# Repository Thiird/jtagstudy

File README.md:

# jtagstudy
In my journey of embedded systems, I felt like I was lacking embedded software development experience, and so to gain some, I decided to implement some of the [JTAG IEE 1149.1](https://en.wikipedia.org/wiki/JTAG) functionalities as [bit-bang](https://en.wikipedia.org/wiki/Bit_banging) routines.

I choose JTAG as the protocol to bit-bang because it's relatively simple to understand, useful for a lot of things used across different architectures and it's an industry standard.

I used AVR MCU's because that's what I had at my disposal, no need to spend extra money on a fancy STM32.

# Overview

Here is a picture of my inital setup:

I used an [ATmega 32u4](http://ww1.microchip.com/downloads/en/DeviceDoc/Atmel-7766-8-bit-AVR-ATmega16U4-32U4_Datasheet.pdf) from an [Arduino Micro](https://store.arduino.cc/products/arduino-micro) board as the the main MCU to which I uploaded code via the [USBasp](https://www.fischl.de/usbasp/) ISP programmer and [avrdude](https://www.nongnu.org/avrdude/). I also implemented the USART interface (TX only) to be able to print to the serial monitor the result of the code.
To test the code, I initially connected the four GPIO bit-banging pins to the JTAG interface of the 32u4 itself, once that was working, I used a custom PCB designed in [KiCad](https://www.kicad.org/) to extend the JTAG chain with two more TAPs and test the code again. The custom PCB is a breakout for another ATmega 32u4 and an [AT90USB1286](http://ww1.microchip.com/downloads/en/DeviceDoc/doc7593.pdf) Extending the JTAG chain revealed some bugs which I managed to solve in a couple of days.

The PCB had some mistakes which were solved by bridging some connections and whatnot.

Here is a picture of my final setup:

I learned a lot of things while doing this project, not only software related, but also hardware, because this was my first time using an [oscilloscope](https://eleshop.eu/owon-sds1104.html), which I used to debug the signals I was bit-banging.

# Functionalities

- **JTAG TAP chain length**

    Uses the **BYPASS** instruction to check how many Test Acces Points (TAP's) are connected to the JTAG interface.

- **IDCODE scan**

    Prints to serial in detail the **IDCODE** of all the TAPs found in the JTAG Chain.

- **JTAG discovery**

    Given a set of GPIO pins, the four JTAG signal (TDI,TDO,TMS,TCK) are applied in different combinations to find if there is a JTAG interface on four of those pins.

# Credits
This was project was inspired by the [JTAGulator](https://github.com/grandideastudio/jtagulator) by Joe Grand.

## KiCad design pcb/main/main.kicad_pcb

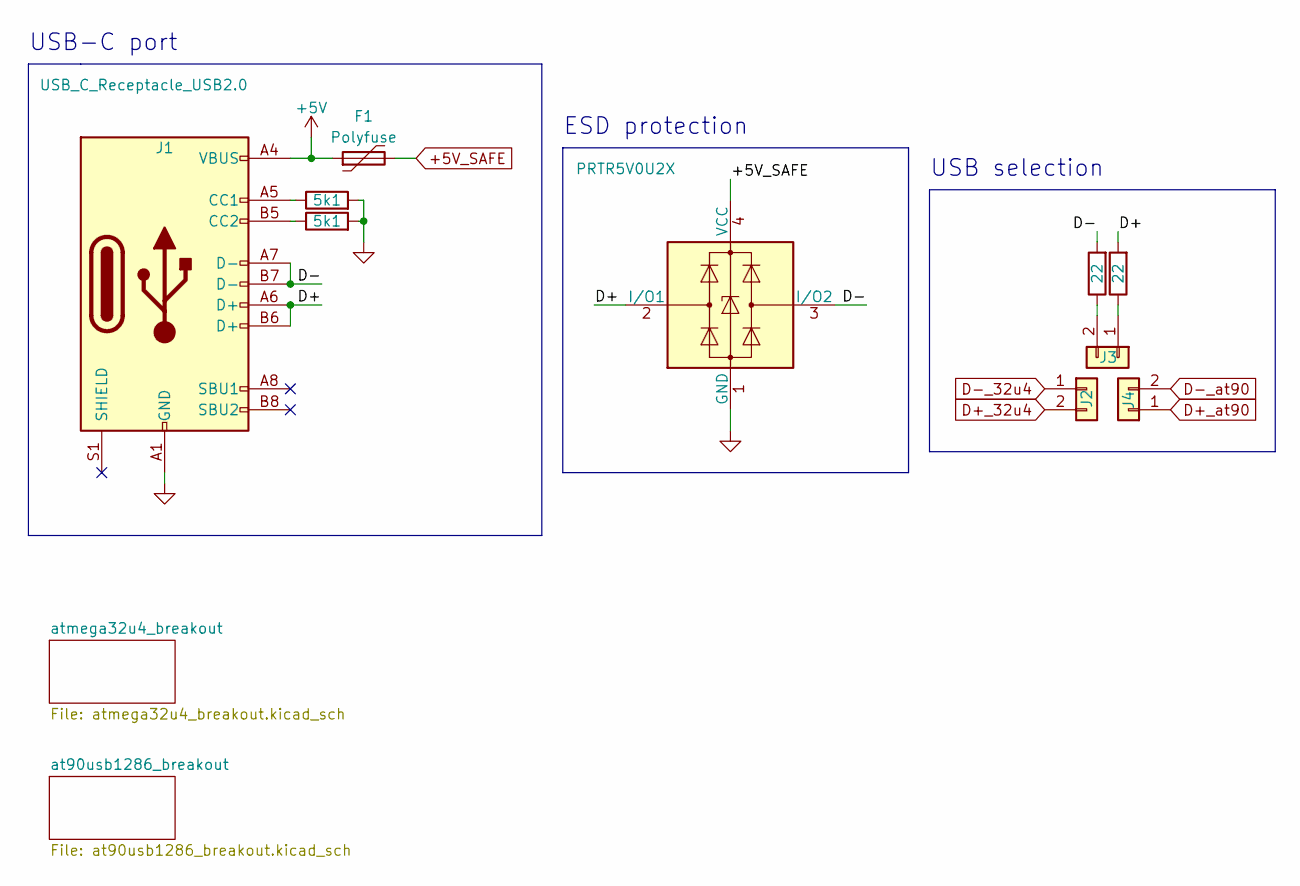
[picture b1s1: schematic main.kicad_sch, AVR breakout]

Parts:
D1: PRTR5V0U2X; SOT-143
F1: Polyfuse; Fuse_0603_1608Metric
J1: USB_C_Receptacle_USB2.0; USB_C_Receptacle_HRO_TYPE-C-31-M-12
J2, J3, J4: Conn_01x02; PinHeader_1x02_P2.54mm_Vertical
R1, R2: 5k1; R_0603_1608Metric
R3, R4: 22; R_0603_1608Metric

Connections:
+5V: F1.1, J1.A4 (VBUS), J1.A9 (VBUS), J1.B4 (VBUS), J1.B9 (VBUS)
+5V_SAFE: D1.4 (VCC), F1.2; also elsewhere on the board
/D+: D1.2 (I/O1), J1.A6 (D+), J1.B6 (D+), R4.2
/D-: D1.3 (I/O2), J1.A7 (D-), J1.B7 (D-), R3.2
D+_32u4: J2.2; also elsewhere on the board
D+_at90: J4.1; also elsewhere on the board
D-_32u4: J2.1; also elsewhere on the board
D-_at90: J4.2; also elsewhere on the board
GND: D1.1 (GND), J1.A1 (GND), J1.A12 (GND), J1.B1 (GND), J1.B12 (GND), R1.2, R2.2; also elsewhere on the board
unnamed: J1.A5 (CC1), R1.1
unnamed: J1.B5 (CC2), R2.1
unnamed: J3.1, R4.1
unnamed: J3.2, R3.1

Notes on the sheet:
ESD protection
USB selection
USB-C port

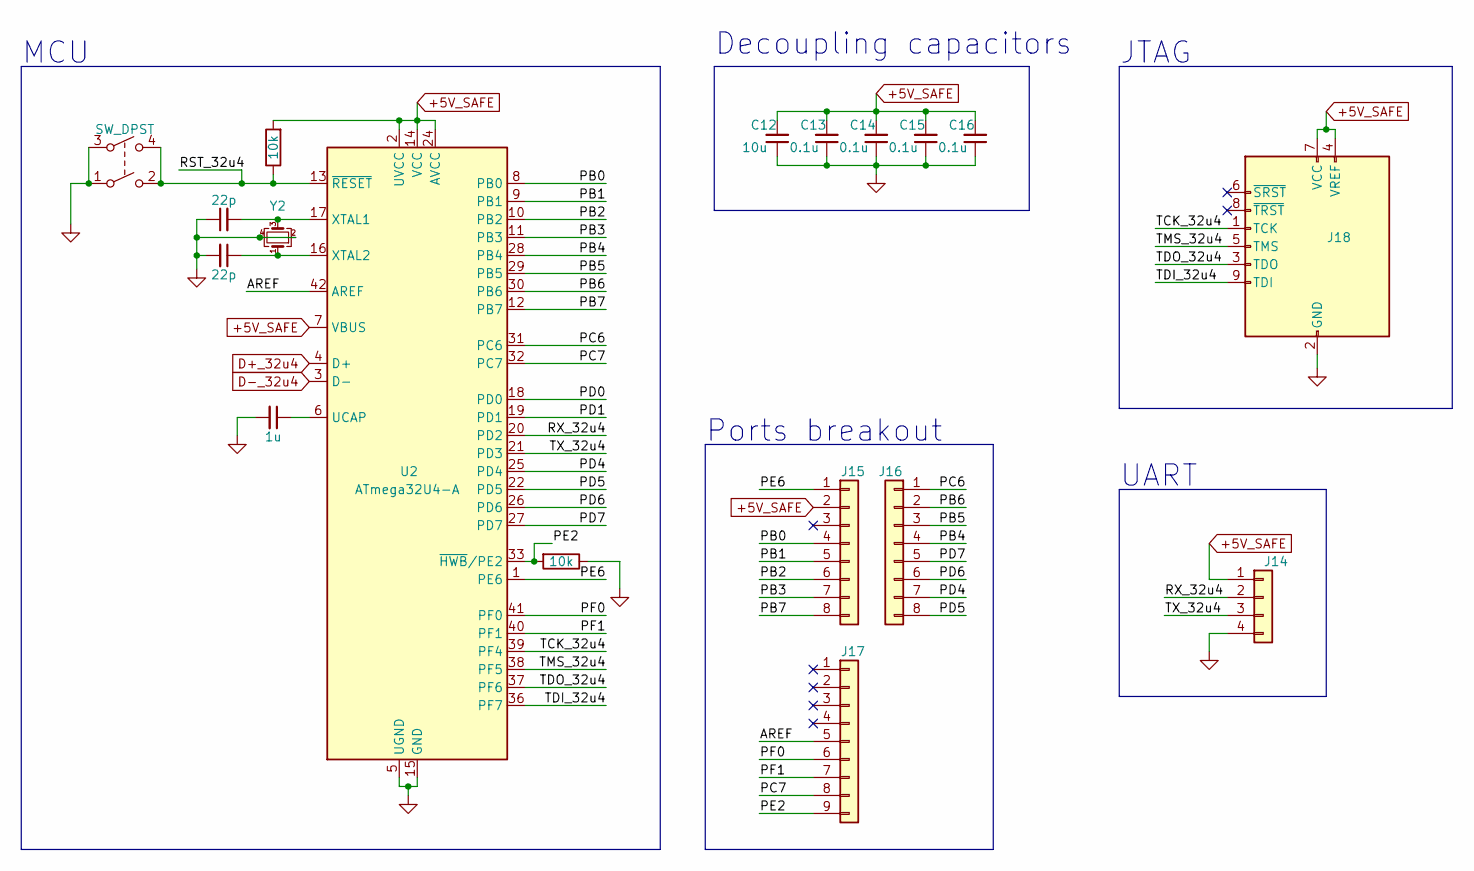
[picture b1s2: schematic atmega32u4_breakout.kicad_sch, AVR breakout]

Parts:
C9, C10: 22p; C_0603_1608Metric
C11: 1u; C_0603_1608Metric
C12: 10u; C_0603_1608Metric
C13, C14, C15, C16: 0.1u; C_0603_1608Metric
J14: Conn_01x04; PinHeader_1x04_P2.54mm_Vertical
J15: Conn_01x08; PinHeader_1x08_P2.54mm_Vertical
J16, J18: (no value)
J17: Conn_01x09; PinHeader_1x09_P2.54mm_Vertical
R7, R8: 10k; R_0603_1608Metric
SW2: SW_DPST; PTS526
U2: ATmega32U4-A; TQFP-44_10x10mm_P0.8mm
Y2: Crystal_GND24_Small; Crystal_SMD_2016-4Pin_2.0x1.6mm

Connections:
+5V_SAFE: C12.2, C13.2, C14.2, C15.2, C16.2, J14.1, J15.2, J18.4 (VREF), J18.7 (VCC), R7.2, U2.2 (UVCC), U2.7 (VBUS), U2.14 (VCC), U2.24 (AVCC), U2.34 (VCC), U2.44 (AVCC); also elsewhere on the board
/atmega32u4_breakout/AREF: J17.5, U2.42 (AREF)
/atmega32u4_breakout/PB0: J15.4, U2.8 (PB0)
/atmega32u4_breakout/PB1: J15.5, U2.9 (PB1)
/atmega32u4_breakout/PB2: J15.6, U2.10 (PB2)
/atmega32u4_breakout/PB3: J15.7, U2.11 (PB3)
/atmega32u4_breakout/PB4: J16.4, U2.28 (PB4)
/atmega32u4_breakout/PB5: J16.3, U2.29 (PB5)
/atmega32u4_breakout/PB6: J16.2, U2.30 (PB6)
/atmega32u4_breakout/PB7: J15.8, U2.12 (PB7)
/atmega32u4_breakout/PC6: J16.1, U2.31 (PC6)
/atmega32u4_breakout/PC7: J17.8, U2.32 (PC7)
/atmega32u4_breakout/PD0: U2.18 (PD0)
/atmega32u4_breakout/PD1: U2.19 (PD1)
/atmega32u4_breakout/PD4: J16.7, U2.25 (PD4)
/atmega32u4_breakout/PD5: J16.8, U2.22 (PD5)
/atmega32u4_breakout/PD6: J16.6, U2.26 (PD6)
/atmega32u4_breakout/PD7: J16.5, U2.27 (PD7)
/atmega32u4_breakout/PE2: J17.9, R8.2, U2.33 (~HWB/PE2)
/atmega32u4_breakout/PE6: J15.1, U2.1 (PE6)
/atmega32u4_breakout/PF0: J17.6, U2.41 (PF0)
/atmega32u4_breakout/PF1: J17.7, U2.40 (PF1)
/atmega32u4_breakout/RST_32u4: R7.1, SW2.2, SW2.4, U2.13 (~RESET)
/atmega32u4_breakout/RX_32u4: J14.2, U2.20 (PD2)
/atmega32u4_breakout/TCK_32u4: J18.1 (TCK), U2.39 (PF4)
/atmega32u4_breakout/TDI_32u4: J18.9 (TDI), U2.36 (PF7)
/atmega32u4_breakout/TDO_32u4: J18.3 (TDO), U2.37 (PF6)
/atmega32u4_breakout/TMS_32u4: J18.5 (TMS), U2.38 (PF5)
/atmega32u4_breakout/TX_32u4: J14.3, U2.21 (PD3)
D+_32u4: U2.4 (D+); also elsewhere on the board
D-_32u4: U2.3 (D-); also elsewhere on the board
GND: C9.1, C10.2, C11.2, C12.1, C13.1, C14.1, C15.1, C16.1, J14.4, J18.2 (GND), J18.10 (GND), R8.1, SW2.1, SW2.3, U2.5 (UGND), U2.15 (GND), U2.23 (GND), U2.35 (GND), U2.43 (GND), Y2.2, Y2.4; also elsewhere on the board
unnamed: C9.2, U2.17 (XTAL1), Y2.3
unnamed: C10.1, U2.16 (XTAL2), Y2.1
unnamed: C11.1, U2.6 (UCAP)

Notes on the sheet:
JTAG
Ports breakout
Decoupling capacitors
UART
MCU

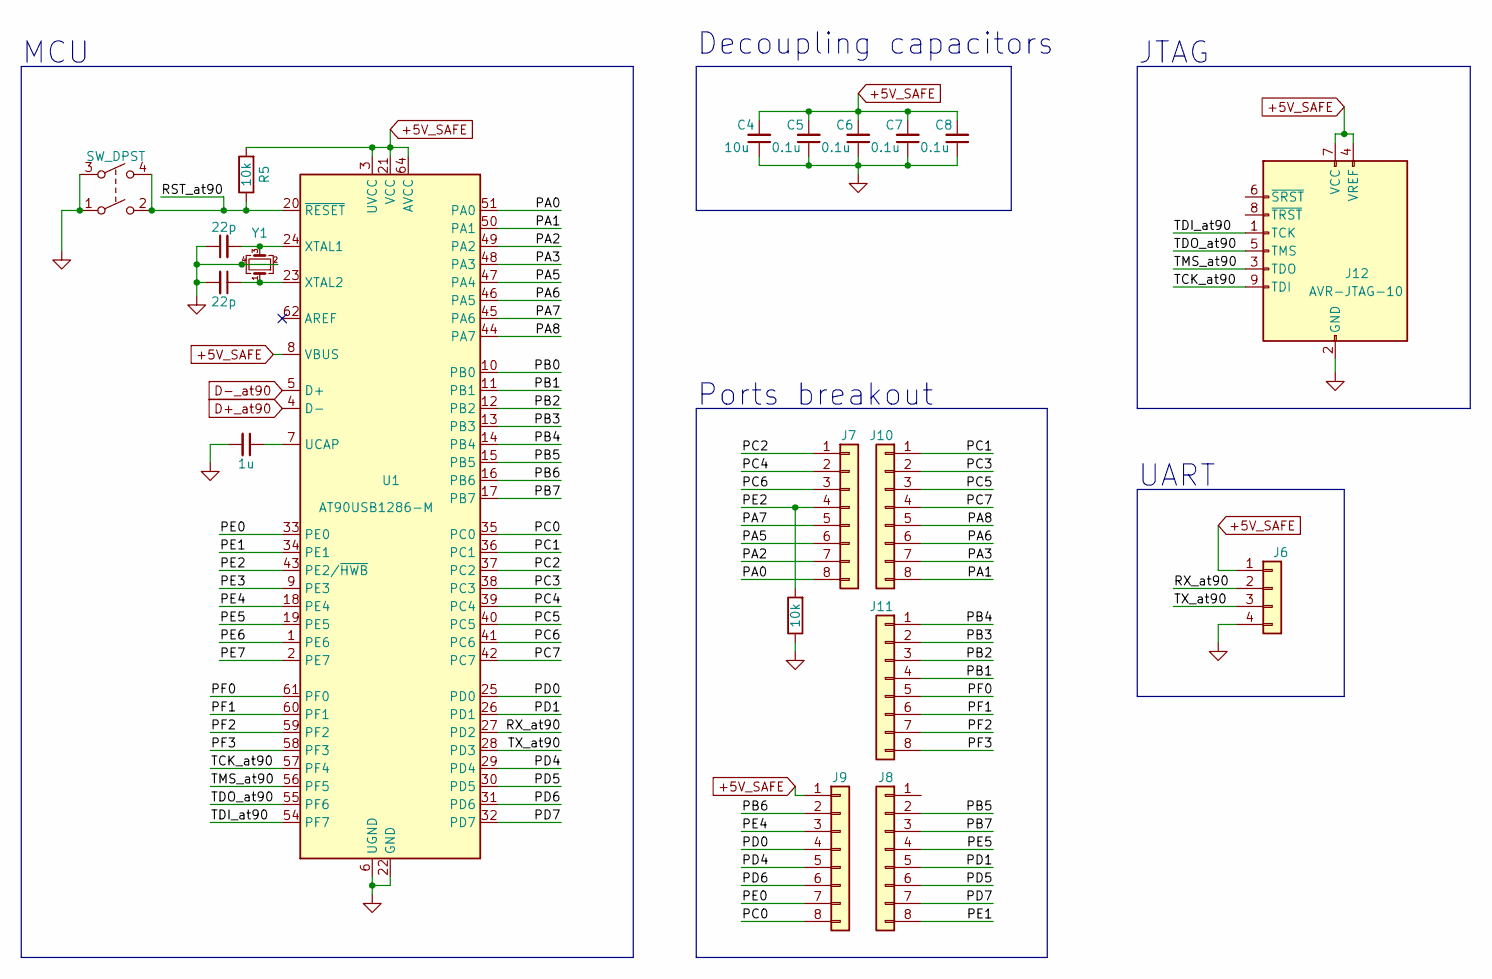
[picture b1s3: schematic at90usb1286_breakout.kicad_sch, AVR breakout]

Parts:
C1, C2: 22p; C_0603_1608Metric
C3: 1u; C_0603_1608Metric
C4: 10u; C_0603_1608Metric
C5, C6, C7, C8: 0.1u; C_0603_1608Metric
J6: Conn_01x04; PinHeader_1x04_P2.54mm_Vertical
J7, J8, J9, J10, J11: Conn_01x08; PinHeader_1x08_P2.54mm_Vertical
J12: AVR-JTAG-10; PinHeader_2x05_P2.54mm_Vertical
R5, R6: 10k; R_0603_1608Metric
SW1: SW_DPST; PTS526
U1: AT90USB1286-M; QFN-64-1EP_9x9mm_P0.5mm_EP7.5x7.5mm
Y1: Crystal_GND24_Small; Crystal_SMD_2016-4Pin_2.0x1.6mm

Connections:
+5V_SAFE: C4.2, C5.2, C6.2, C7.2, C8.2, J6.1, J9.1, J12.4 (VREF), J12.7 (VCC), R5.2, U1.3 (UVCC), U1.8 (VBUS), U1.21 (VCC), U1.52 (VCC), U1.64 (AVCC); also elsewhere on the board
/at90usb1286_breakout/PA0: J7.8, U1.51 (PA0)
/at90usb1286_breakout/PA1: J10.8, U1.50 (PA1)
/at90usb1286_breakout/PA2: J7.7, U1.49 (PA2)
/at90usb1286_breakout/PA3: J10.7, U1.48 (PA3)
/at90usb1286_breakout/PA5: J7.6, U1.47 (PA4)
/at90usb1286_breakout/PA6: J10.6, U1.46 (PA5)
/at90usb1286_breakout/PA7: J7.5, U1.45 (PA6)
/at90usb1286_breakout/PA8: J10.5, U1.44 (PA7)
/at90usb1286_breakout/PB0: U1.10 (PB0)
/at90usb1286_breakout/PB1: J11.4, U1.11 (PB1)
/at90usb1286_breakout/PB2: J11.3, U1.12 (PB2)
/at90usb1286_breakout/PB3: J11.2, U1.13 (PB3)
/at90usb1286_breakout/PB4: J11.1, U1.14 (PB4)
/at90usb1286_breakout/PB5: J8.2, U1.15 (PB5)
/at90usb1286_breakout/PB6: J9.2, U1.16 (PB6)
/at90usb1286_breakout/PB7: J8.3, U1.17 (PB7)
/at90usb1286_breakout/PC0: J9.8, U1.35 (PC0)
/at90usb1286_breakout/PC1: J10.1, U1.36 (PC1)
/at90usb1286_breakout/PC2: J7.1, U1.37 (PC2)
/at90usb1286_breakout/PC3: J10.2, U1.38 (PC3)
/at90usb1286_breakout/PC4: J7.2, U1.39 (PC4)
/at90usb1286_breakout/PC5: J10.3, U1.40 (PC5)
/at90usb1286_breakout/PC6: J7.3, U1.41 (PC6)
/at90usb1286_breakout/PC7: J10.4, U1.42 (PC7)
/at90usb1286_breakout/PD0: J9.4, U1.25 (PD0)
/at90usb1286_breakout/PD1: J8.5, U1.26 (PD1)
/at90usb1286_breakout/PD4: J9.5, U1.29 (PD4)
/at90usb1286_breakout/PD5: J8.6, U1.30 (PD5)
/at90usb1286_breakout/PD6: J9.6, U1.31 (PD6)
/at90usb1286_breakout/PD7: J8.7, U1.32 (PD7)
/at90usb1286_breakout/PE0: J9.7, U1.33 (PE0)
/at90usb1286_breakout/PE1: J8.8, U1.34 (PE1)
/at90usb1286_breakout/PE2: J7.4, R6.2, U1.43 (PE2/~HWB)
/at90usb1286_breakout/PE3: U1.9 (PE3)
/at90usb1286_breakout/PE4: J9.3, U1.18 (PE4)
/at90usb1286_breakout/PE5: J8.4, U1.19 (PE5)
/at90usb1286_breakout/PE6: U1.1 (PE6)
/at90usb1286_breakout/PE7: U1.2 (PE7)
/at90usb1286_breakout/PF0: J11.5, U1.61 (PF0)
/at90usb1286_breakout/PF1: J11.6, U1.60 (PF1)
/at90usb1286_breakout/PF2: J11.7, U1.59 (PF2)
/at90usb1286_breakout/PF3: J11.8, U1.58 (PF3)
/at90usb1286_breakout/RST_at90: R5.1, SW1.2, SW1.4, U1.20 (~RESET)
/at90usb1286_breakout/RX_at90: J6.2, U1.27 (PD2)
/at90usb1286_breakout/TCK_at90: J12.9 (TDI), U1.57 (PF4)
/at90usb1286_breakout/TDI_at90: J12.1 (TCK), U1.54 (PF7)
/at90usb1286_breakout/TDO_at90: J12.5 (TMS), U1.55 (PF6)
/at90usb1286_breakout/TMS_at90: J12.3 (TDO), U1.56 (PF5)
/at90usb1286_breakout/TX_at90: J6.3, U1.28 (PD3)
D+_at90: U1.4 (D-); also elsewhere on the board
D-_at90: U1.5 (D+); also elsewhere on the board
GND: C1.1, C2.2, C3.2, C4.1, C5.1, C6.1, C7.1, C8.1, J6.4, J12.2 (GND), J12.10 (GND), R6.1, SW1.1, SW1.3, U1.6 (UGND), U1.22 (GND), U1.53 (GND), U1.63 (GND), U1.65 (GND), Y1.2, Y1.4; also elsewhere on the board
unnamed: C1.2, U1.24 (XTAL1), Y1.3
unnamed: C2.1, U1.23 (XTAL2), Y1.1
unnamed: C3.1, U1.7 (UCAP)

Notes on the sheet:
Ports breakout
MCU
JTAG
UART
Decoupling capacitors

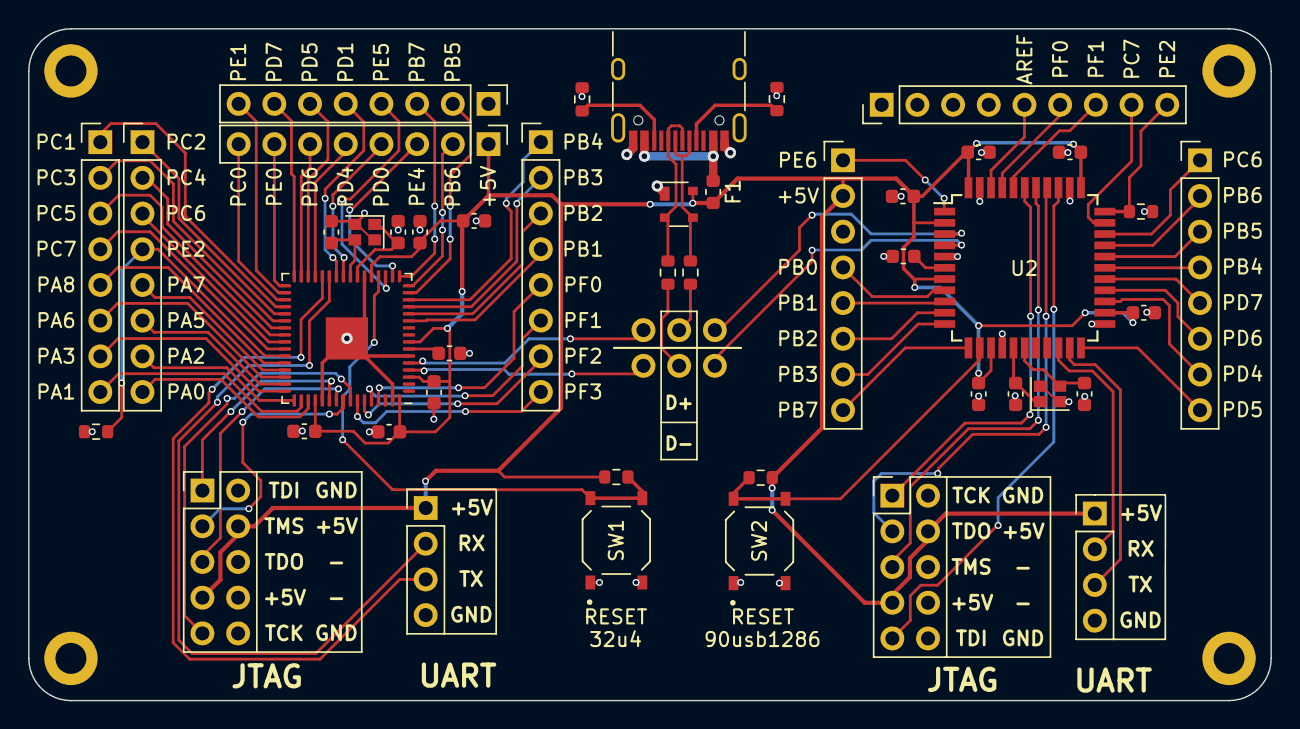
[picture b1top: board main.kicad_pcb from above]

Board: 2 copper layers, 88.4 x 47.8 mm, 48 parts (0 on the bottom side), 90 nets.

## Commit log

2022-04-29 Added pcb folder
2022-05-15 Added BARE METAL led blink example
2022-05-20 Started to implement jtag functions
2022-05-23 Started usart comms
2022-05-24 Polished project and code
2022-05-25 Fixed usart init and tested ISR triggering
2022-05-26 Made usart accept strings longer than it
2022-05-26 code cleanup
2022-05-27 Complete USART TX example
2022-05-28 Added fuses reading and JTAGEN fue write capability
2022-05-28 Added higher level usartSend fucntion, fixed and tested TDO input
2022-06-23 Progress in jtag fsm
2022-06-26 Bypass instruction works on a single mcu
2022-06-28 Started IDCODE scan
2022-06-29 Fixed bug in USART TX, finished IDCODE scan
2022-07-02 Started code refactor to add interface discovery functionality
2022-07-02 Progress
2022-07-02 refactor complete, jtag discovery to be tested
2022-07-02 Fixed messed up git
2022-07-03 Fixed register assignment
2022-07-04 Added more seriuous BYPASS scan routine, written README
2022-07-04 Grammar and whatnot
2022-07-05 Fix README
